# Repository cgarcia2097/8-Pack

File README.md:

# 8-Pack

Inspired by [di0ib's Six Pack design](http://www.40percent.club/2017/04/six-pack-10.html), this keypad project is intended for me on learning how to use KiCAD by extending their design to 8 keys. Mishaps, snafus and foobars expected and incoming.

## Features

### PCB

  - 8 keys, directly connected to MCU pins
  - 8 backlight LEDs, individually addresssable
  - Powered by the Pro Micro
  - Alps or MX button support
  - Runs on a simple Arduino sketch, or optionally QMK firmware

### Plates
  - WS2812 strip underglow support, inspired by [di0db's Gherkin ALPS underglow](http://www.40percent.club/2017/08/gherkin-alps-11.html)

## Third-party firmware ports

- Official QMK port, courtesy of [gorbachev](https://github.com/gorbachev)
  - Rev. 1.1 : [Link](https://github.com/qmk/qmk_firmware/tree/master/keyboards/8pack/rev11)
  - Rev. 1.2 : [Link](https://github.com/qmk/qmk_firmware/tree/master/keyboards/8pack/rev12)

## Assembly guides

Assembly guide can be found here: [GUIDE](ASSEMBLY.md)

## Programming guides

Programming guide can be found here: [GUIDE](PROGRAMMING.md)

## Updates

Updates are posted here: [UPDATES](UPDATES.md)

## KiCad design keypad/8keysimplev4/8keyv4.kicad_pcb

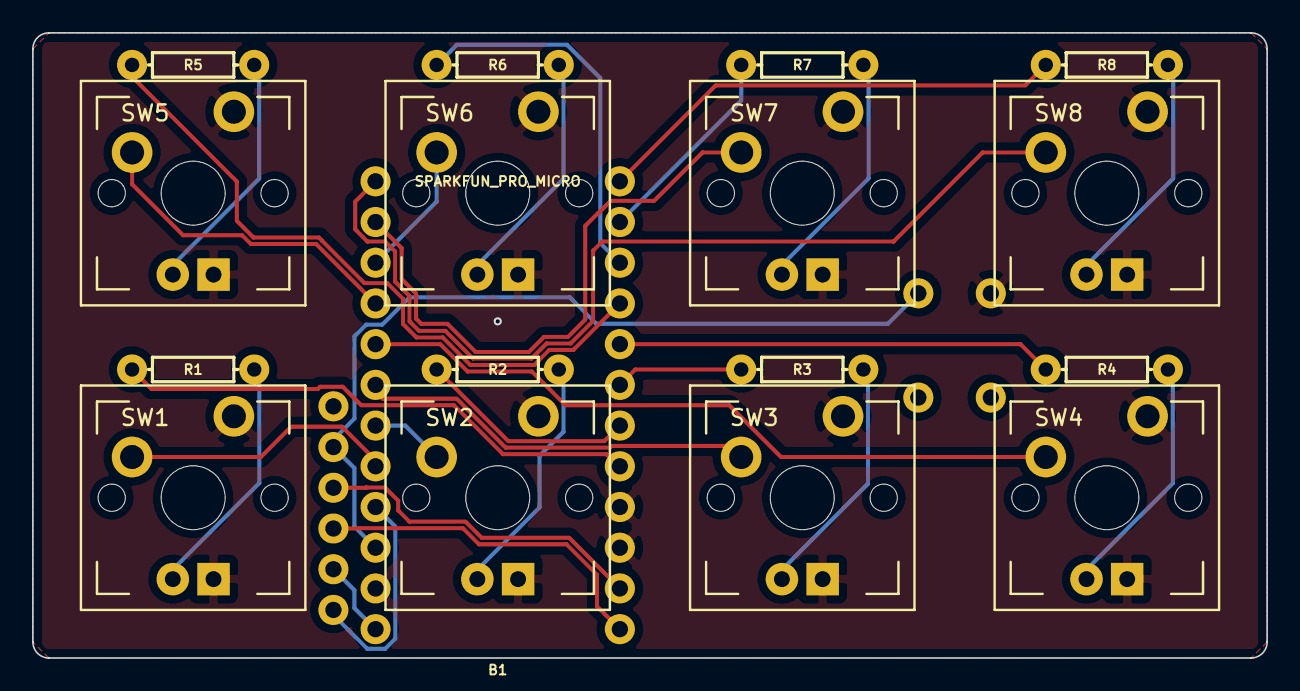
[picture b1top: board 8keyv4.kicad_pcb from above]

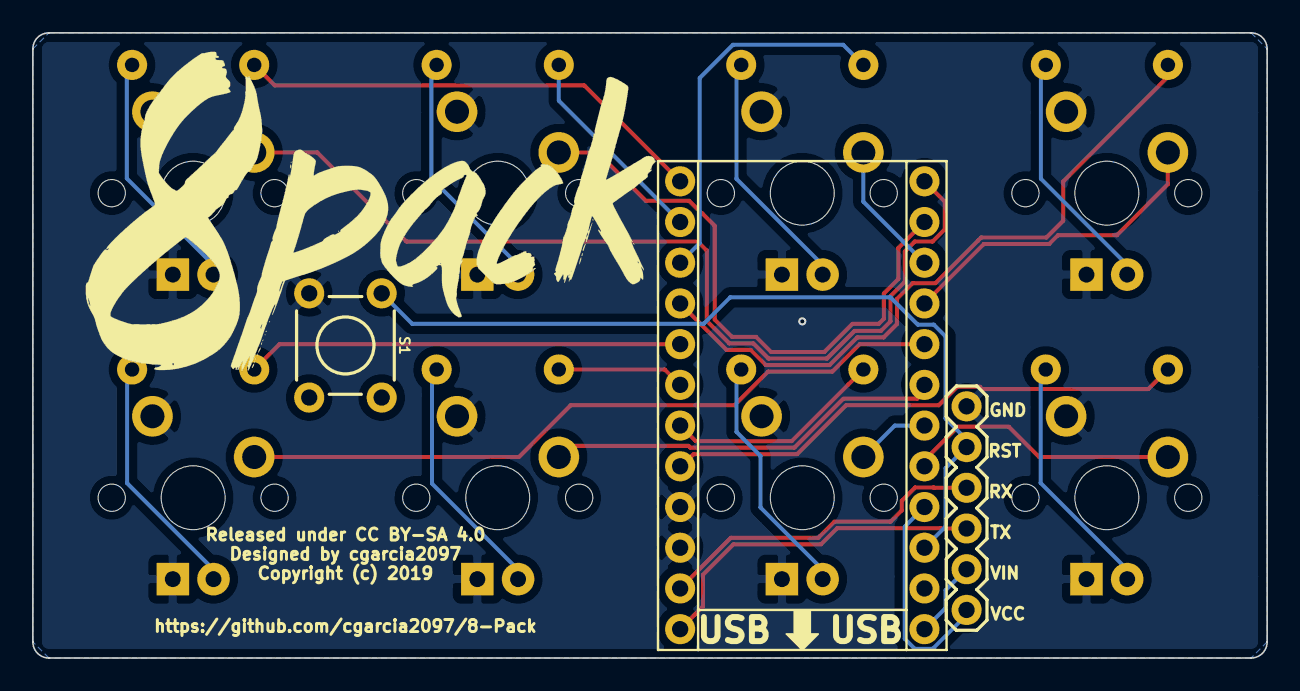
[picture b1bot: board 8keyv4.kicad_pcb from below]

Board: 2 copper layers, 77.0 x 39.0 mm, 19 parts (2 on the bottom side), 30 nets.

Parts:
B1: SPARKFUN_PRO_MICRO
J1: CONN_06NO_SILK_FEMALE_PTH; 1X06
R1, R2, R3, R4, R5, R6, R7, R8: RESISTORAXIAL-0.3; AXIAL-0.3
S1: MOMENTARY-SWITCH-SPST-PTH-6.0MM; TACTILE_SWITCH_PTH_6.0MM
SW1, SW2, SW3, SW4, SW5, SW6, SW7, SW8: MOMENTARY-SWITCH-SPST-LED-PTH-CHERRY; MX_LED

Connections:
GND: B1.3, B1.4, B1.23, J1.6, S1.3, SW1.K, SW1.S2, SW2.K, SW2.S2, SW3.K, SW3.S2, SW4.K, SW4.S2, SW5.K, SW5.S2, SW6.K, SW6.S2, SW7.K, SW7.S2, SW8.K, SW8.S2
KEY1: B1.20, SW1.S1
KEY2: B1.19, SW2.S1
KEY3: B1.18, SW3.S1
KEY4: B1.17, SW4.S1
KEY5: B1.16, SW5.S1
KEY6: B1.15, SW6.S1
KEY7: B1.14, SW7.S1
KEY8: B1.13, SW8.S1
LED1: B1.5, R1.P$1
LED2: B1.6, R2.P$1
LED3: B1.7, R3.P$1
LED4: B1.8, R4.P$1
LED5: B1.9, R5.P$1
LED6: B1.10, R6.P$1
LED7: B1.11, R7.P$1
LED8: B1.12, R8.P$1
unnamed: R1.P$2, SW1.A
unnamed: R2.P$2, SW2.A
unnamed: R3.P$2, SW3.A
unnamed: R4.P$2, SW4.A
unnamed: R5.P$2, SW5.A
unnamed: R6.P$2, SW6.A
unnamed: R7.P$2, SW7.A
unnamed: R8.P$2, SW8.A
RESET: B1.22, J1.5, S1.1
RX: B1.2, J1.4
TX: B1.1, J1.3
VCC: B1.21, J1.1
VIN: B1.24, J1.2

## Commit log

2018-09-28 Getting used to Github
    Doing some cleanups
2019-02-20 Added version 1.1 of PCB
2019-02-23 Reorganizing
2019-02-23 Released under MIT License
2019-02-23 Re-released under MIT LLicense
2019-02-23 Reorganized some files
2019-02-23 Re-released under MIT License
2019-02-23 Added extra detail to the update
2019-03-05 Updated to include warning
2019-03-05 Added rough BOM. Does not include cost of cases
2019-03-11 Uploaded Case Files and Assembly Images
2019-03-11 Fixed folder naming issue on "Ver 1.1/instructions/13-..."
2019-03-11 Added explanation to folder structure.
2019-03-29 Added new plates update
2019-03-29 Added plate version 1.0
2019-03-29 Photo Gallery
2019-03-29 Added pictures to main README
2019-03-31 Added zip files for ordering PCBs online
2019-03-31 Added example for use with the underglow plates
2019-03-31 Consolidated keypad PCB files
2019-03-31 Fixed links for downloading gerber files
2019-04-16 Create ASSEMBLY GUIDE
2019-04-17 Update ASSEMBLY GUIDE
2019-04-17 Updated the skeleton tutorial.
2019-04-17 Rename ASSEMBLY GUIDE to ASSEMBLY
2019-04-17 Added Github config files
2019-04-17 Set theme jekyll-theme-cayman
2019-04-17 Rename ASSEMBLY to ASSEMBLY.md
2019-04-18 Removed Programmind Section
2019-04-21 Updates moved here
2019-04-21 De-cluttered README into seperate pages
2019-04-21 Added missing photos
2019-04-21 Added libraries and Ver 1.2
2019-04-21 Fixed broken links
2019-04-21 Changed image links to relative links
2019-04-21 Fixed the broken links
2019-04-21 New update Apr. 20
2019-04-22 Filled the skeleton parts with instructions
2019-04-22 Added photos
2019-04-22 Fixed pics
2019-04-22 Added disclaimer on top
2019-04-22 Fixed terms in 'Tools required'
2019-04-25 Added non-rgb build
2019-04-28 Included Arduino steps
2020-04-02 Restructured project repository
2020-04-02 Updated Assembly.md
2020-04-02 Added more photos
2020-04-02 Added new photo
2020-04-02 Updated Asembly.md
2020-04-02 Updated README and UPDATES
2020-04-09 Added new project files
2020-04-20 Added final updates to prog guide
2020-04-20 Added programming photos
2020-04-20 reorganized project images
2020-07-07 Fixed broken image links
2020-07-07 Updated README, UPDATES, images
2020-07-07 Updated ASSEMBLY and UPDATES

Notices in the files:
keypad/8keysimplev4/8keyv4.kicad_pcb:
Released under CC BY-SA 4.0
Copyright (c) 2019
